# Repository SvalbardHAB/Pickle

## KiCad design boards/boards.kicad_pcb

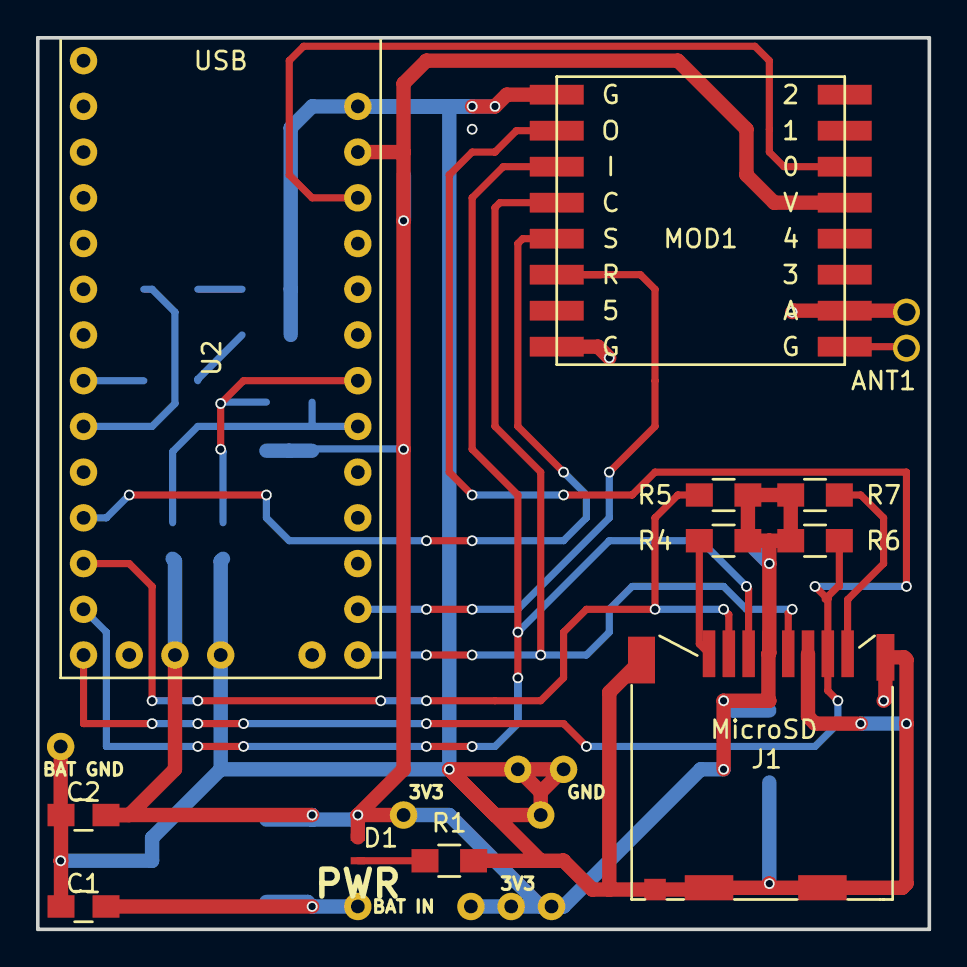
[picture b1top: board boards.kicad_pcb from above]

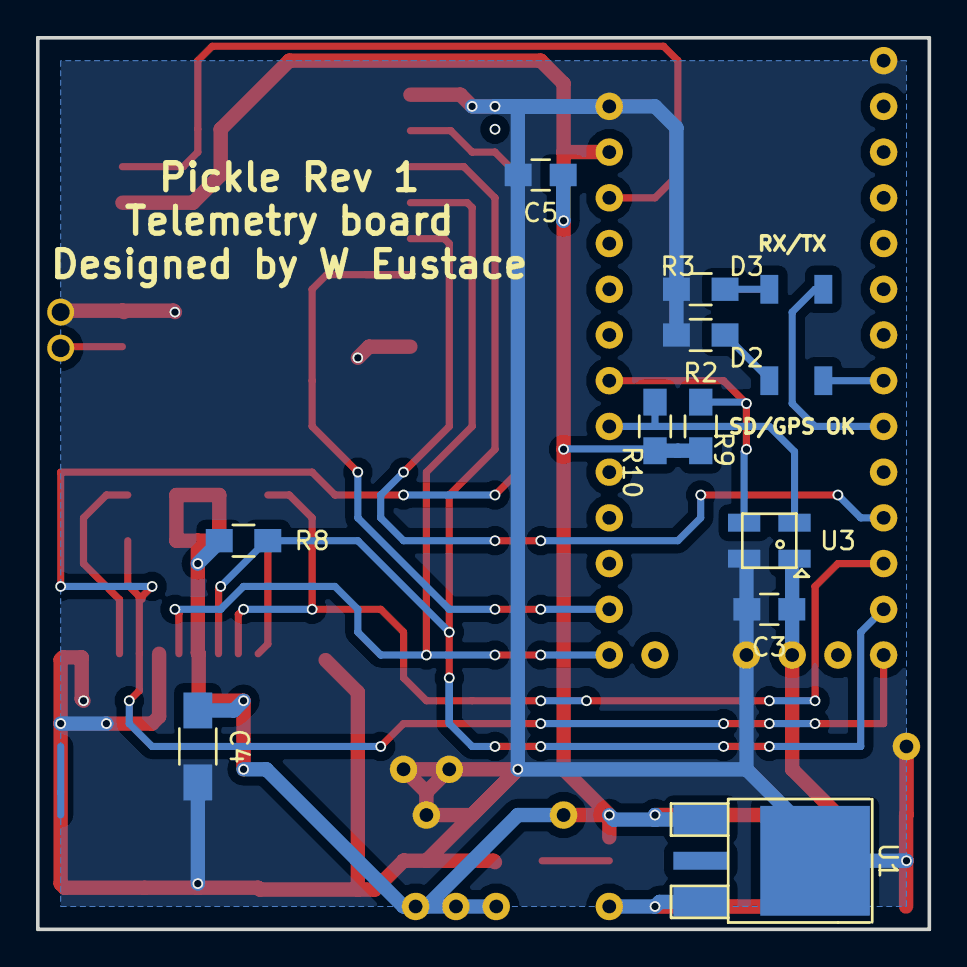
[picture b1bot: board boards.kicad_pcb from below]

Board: 2 copper layers, 49.5 x 49.5 mm, 33 parts (12 on the bottom side), 19 nets.

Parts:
ANT1: ANT; ANT_50ohm
C1, C2, C3, C5: 4.7uF; C_0805_HandSoldering
C4: 22uF; C_1206_HandSoldering
D1: LED; KPH-1608SGC
D2, D3: LED; KingbrightKPTL-3216QBC-D-01
J1: MicroSD; DM3CS-SF
MOD1: RFM_9xW; RFM9xW
P14, P15, P16, P17, P18, P19, P20, P21, P22: CONN_01X01; single_pad
R1, R2, R3: 470; R_0805_HandSoldering
R4, R5, R6, R7, R8: 47k; R_0805_HandSoldering
R9, R10: 2.2k; R_0805_HandSoldering
U1: LP38690; TO-252-3Lead
U2: Teensy_LC; Teensy-LC
U3: MS5637

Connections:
+3V3: C2.1, C3.1, C4.1, C5.1, D1.2, J1.4, MOD1.13, P18.1, P19.1, P20.1, P21.1, R4.1, R5.1, R6.1, R7.1, R8.1, R9.1, R10.1, U1.1, U2.24, U2.25, U3.1
GND: ANT1.2, C1.2, C2.2, C3.2, C4.2, C5.2, J1.6, J1.S, MOD1.1, MOD1.8, MOD1.10, P14.1, P15.1, P16.1, P17.1, R1.2, R2.2, R3.2, U1.2, U2.27, U2.28, U2.29, U3.4
unnamed: D1.1, R1.1
unnamed: D2.1, R2.1
unnamed: D2.2, U2.6
unnamed: D3.1, R3.1
unnamed: D3.2, U2.7
unnamed: J1.1, R4.2
unnamed: J1.2, R5.2, U2.10
unnamed: J1.3, MOD1.3, R8.2, U2.11
unnamed: J1.5, MOD1.4, U2.13
unnamed: J1.7, MOD1.2, R6.2, U2.12
unnamed: J1.8, R7.2
unnamed: MOD1.5, U2.9
unnamed: MOD1.6, U2.14
unnamed: MOD1.14, U2.23
SCL: R10.2, U2.19, U3.3
SDA: R9.2, U2.18, U3.2
VCC: C1.1, P22.1, U1.3

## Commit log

2016-07-04 Created project; designed power supply.
2016-07-06 Schematics completed (rev 1). PCB layout started.
2016-07-06 Continued routing SPI pins. Added some relevant offline docs.
2016-07-09 Completed SPI connections
2016-07-11 Changed to TO252 power reg. Continued trace connection.
2016-07-11 Continued PCB layout.
2016-07-12 Added power smoothing caps around board.
2016-07-12 Completed design. Not yet checked/verified.
2016-07-12 DRC passed.
2016-07-16 Final modifications to Rev.1 and exported Gerbers.
2016-07-17 Added parts list and zipped Gerbers ready for submission to Elecrow
2016-08-29 Experimentation with TDMA transmission and reception
2016-08-30 Bugfixes. (...)
    Fixed EEPROM writer LED. Fixed occasional TDMA sync timing bug by altering sync mechanism. Now tested and appears reliable w/ three devices at least!
2016-09-01 Tidied. Added GPS & photodiode code.
2016-09-01 Refinement & other tweaking
2016-09-02 Minor changes to packet structure
2016-09-02 Fixed GPS transmission. Temperature in one byte.
2016-09-02 Revised status criteria & added status byte generation code
2016-09-03 Added reset & frequency change if recovery sync failed.
2016-09-03 Fixed receiver, GPS chips etc.
2016-09-04 Continuing pre-launch tweaks
2016-09-04 Continuing pre-launch tweaks.
